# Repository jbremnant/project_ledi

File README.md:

ledi
====

LED Interface (ledi) is an interactive LED display that can communicate with bluetooth devices as well as PC's

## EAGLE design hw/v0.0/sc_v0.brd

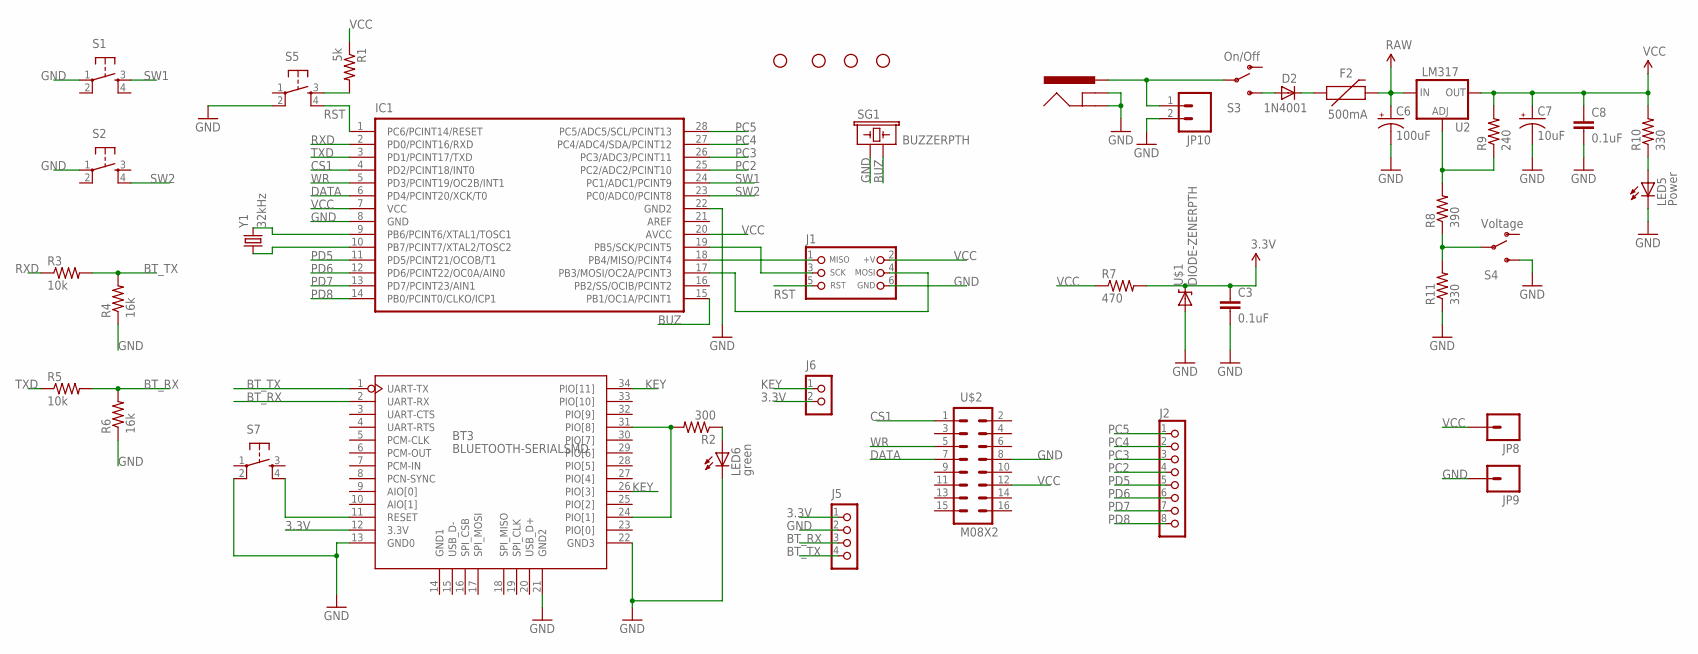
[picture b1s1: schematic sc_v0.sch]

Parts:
BT3: BLUETOOTH-SERIALSMD; SERIAL_BLUETEETH
C3, C8: 0.1uF; CAP-PTH-SMALL2
C6: 100uF; CPOL-RADIAL-100UF-25V
C7: 10uF; CPOL-RADIAL-10UF-25V
D2: 1N4001; DIODE-0.4
F2: 500mA; PTC
IC1: IC_UC_ATMEGA328PDIL; DIL28-N
J1: CON_HEADER_PRG_AVR_ICSP; HEADER_PRG_2X03
J2: CON_HEADER_1X08-PTH; M1X8
J3: POWER_JACKPTH; POWER_JACK_PTH
J5: CON_HEADER_1X04; M1X4
J6: CON_HEADER_1X02-PTH; M1X2
JP1, JP2, JP3, JP4: STAND-OFF
JP8, JP9: M01PTH; 1X01
JP10: M02PTH; 1X02
LED5: Power; LED5MM
LED6: green; LED3MM
R1: 5k; AXIAL-0.3
R2: 300; AXIAL-0.3
R3, R5: 10k; AXIAL-0.3
R4, R6: 16k; AXIAL-0.3
R7: 470; AXIAL-0.3
R8: 390; AXIAL-0.3
R9: 240; AXIAL-0.3
R10, R11: 330; AXIAL-0.3
S1, S2, S5, S7: TAC_SWITCHPTH; TACTILE-PTH
S3: On/Off; SWITCH-SPST
S4: Voltage; SWITCH-SPST
SG1: BUZZERPTH; BUZZER-12MM
U2: LM317; TO220-ADJ
U$1: DIODE-ZENERPTH; DIODE-ZENER
U$2: M08X2; 2X8
Y1: 32kHz; TC38H

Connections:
3.3V: BT3.12 (3.3V), C3.1, J5.1, J6.2, R7.P$2 (2), U$1.P$1 (C)
BT_RX: BT3.2 (UART-RX), J5.3, R5.P$2 (2), R6.P$2 (2)
BT_TX: BT3.1 (UART-TX), J5.4, R3.P$2 (2), R4.P$2 (2)
BUZ: IC1.15 (PB1/OC1A/PCINT1), SG1.- (2)
CS1: IC1.4 (PD2/PCINT18/INT0), U$2.1
DATA: IC1.6 (PD4/PCINT20/XCK/T0), U$2.7
GND: BT3.13 (GND0), BT3.21 (GND2), BT3.22 (GND3), C3.2, C6.2 (-), C7.2 (-), C8.2, IC1.8 (GND), IC1.22 (GND2), J1.6 (GND), J3.GND, J3.GNDBREAK, J5.2, JP9.1, JP10.2, LED5.K (C), LED6.K (C), R4.P$1 (1), R6.P$1 (1), R11.P$1 (1), S1.1, S2.1, S4.3 (S), S5.2, S7.2, SG1.+ (1), U$1.P$2 (A), U$2.8
KEY: BT3.26 (PIO[3]), BT3.34 (PIO[11]), J6.1
unnamed: IC1.9 (PB6/PCINT6/XTAL1/TOSC1), Y1.2
unnamed: IC1.10 (PB7/PCINT7/XTAL2/TOSC2), Y1.1
unnamed: IC1.18 (PB4/MISO/PCINT4), J1.1 (MISO)
unnamed: IC1.19 (PB5/SCK/PCINT5), J1.3 (SCK)
unnamed: IC1.17 (PB3/MOSI/OC2A/PCINT3), J1.4 (MOSI)
unnamed: R8.P$2 (2), R9.P$1 (1), U2.ADJ
unnamed: LED5.A, R10.P$1 (1)
unnamed: BT3.24 (PIO[1]), BT3.31 (PIO[8]), R2.P$2 (2)
unnamed: D2.C, F2.P$1 (1)
unnamed: D2.A, S3.3 (S)
unnamed: J3.PWR, JP10.1, S3.2
unnamed: R8.P$1 (1), R11.P$2 (2), S4.2
unnamed: R1.P$2 (2), S5.3
unnamed: BT3.11 (RESET), S7.4
unnamed: LED6.A, R2.P$1 (1)
PC2: IC1.25 (PC2/ADC2/PCINT10), J2.4
PC3: IC1.26 (PC3/ADC3/PCINT11), J2.3
PC4: IC1.27 (PC4/ADC4/SDA/PCINT12), J2.2
PC5: IC1.28 (PC5/ADC5/SCL/PCINT13), J2.1
PD5: IC1.11 (PD5/PCINT21/OCOB/T1), J2.5
PD6: IC1.12 (PD6/PCINT22/OC0A/AIN0), J2.6
PD7: IC1.13 (PD7/PCINT23/AIN1), J2.7
PD8: IC1.14 (PB0/PCINT0/CLKO/ICP1), J2.8
RAW: C6.1 (+), F2.P$2 (2), U2.IN
RST: IC1.1 (PC6/PCINT14/RESET), J1.5 (RST), S5.4
RXD: IC1.2 (PD0/PCINT16/RXD), R3.P$1 (1)
SW1: IC1.24 (PC1/ADC1/PCINT9), S1.3
SW2: IC1.23 (PC0/ADC0/PCINT8), S2.4
TXD: IC1.3 (PD1/PCINT17/TXD), R5.P$1 (1)
VCC: C7.1 (+), C8.1, IC1.7 (VCC), IC1.20 (AVCC), J1.2 (+V), JP8.1, R1.P$1 (1), R7.P$1 (1), R9.P$2 (2), R10.P$2 (2), U2.OUT, U$2.12
WR: IC1.5 (PD3/PCINT19/OC2B/INT1), U$2.5

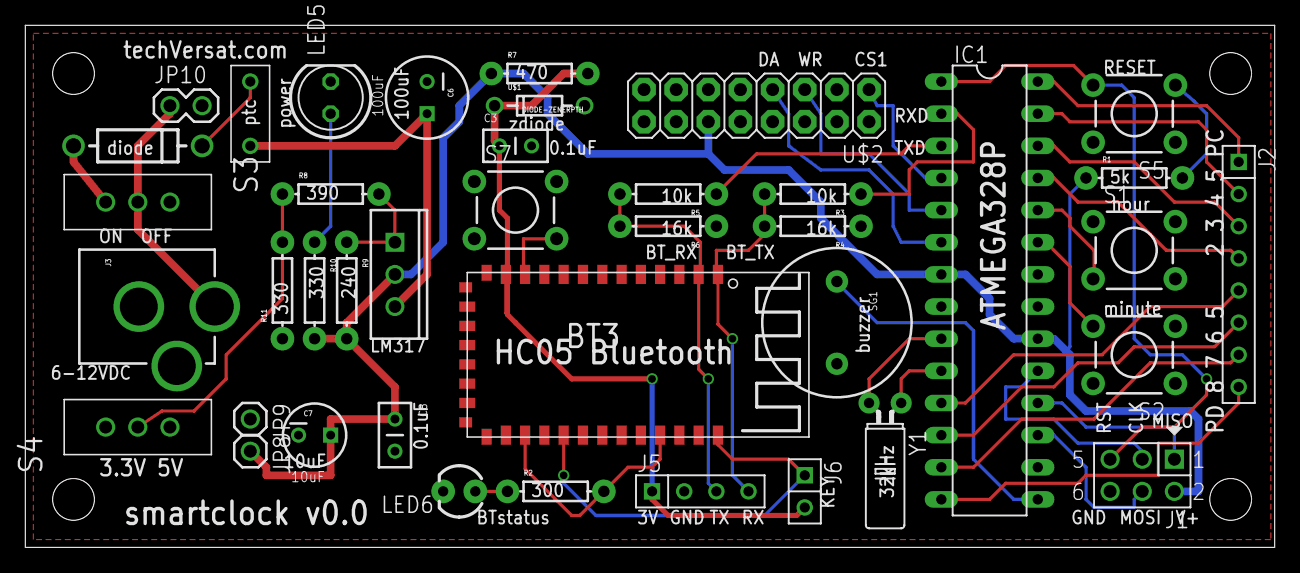
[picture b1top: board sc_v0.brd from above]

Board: 2 copper layers, 98.7 x 41.3 mm, 44 parts (0 on the bottom side), 39 nets.

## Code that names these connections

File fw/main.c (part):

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
// #define USE_V0

#define BUTTON1 PC1
#define BUTTON2 PC0

#ifdef USE_V0
  #define BUZZER_PORT PORTB
  #define BUZZER_REG  DDRB
  #define BUZZER      PB1
#else
  #define BUZZER_PORT PORTD
  #define BUZZER_REG  DDRD
  #define BUZZER      PD6
#endif

#define BT_PRESS 0x02
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ISR(TIMER0_COMPA_vect)
{
  sei();  // enable so we become interruptible
  PORTC ^= (1<<PC4);
  ht1632_syncram_fast(); 
}

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  //  //PCINT14...8 see p70 of datasheet
  PCICR |= (1<<PCIE1);

  //Set the mask on Pin change interrupt 1 so that only PCINT12 (PC4) triggers
  //the interrupt. see p71 of datasheet
  // PCINT17 (PD1) for hours, PCINT19 (PD3) for minutes
  // PC1 / ADC1 / PCINT9
  // PC0 / ADC0 / PCINT8
  PCMSK1 |= (1<<PCINT9) | (1<<PCINT8);

  DDRC  &= ~(1<<BUTTON1);
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
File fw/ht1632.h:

#ifndef _HT1632_HEADER
#define _HT1632_HEADER

#include <avr/io.h>

// for other compilers without uint8_t, change this to char
#define byte  uint8_t
#define byte2 uint16_t

// modify here for more boards
#define N_PANELS    2
#define ALL_BOARDS  0b00000011   // bit mask for active display boards

#define OUTPUT 1
#define INPUT  0
// redefine these macros as necessary : can use ## to concat macro function params
#define PIN_MODE(X,Y,MODE)  if(MODE==1) X |= (1<<Y); else X &= ~(1<<Y)
#define PIN_SET_HIGH(X,Y)   X |= (1<<Y)
#define PIN_SET_LOW(X,Y)    X &= ~(1<<Y)
#define PIN_GET(X,Y)        ( X & (1<<Y) )

// configure stuff here
#define CS1_PORT    PORTD  // CS BoardSelect
#define CS2_PORT    PORTD  // CS BoardSelect
#define RD_PORT     PORTD  // Read Clock
#define WR_PORT     PORTD  // Write Clock
#define DAT_PORT    PORTD  // Write Data
#define DAT_PORT_RD PIND   // Read Data

#define CS1_REG     DDRD
#define CS2_REG     DDRD
#define RD_REG      DDRD
#define WR_REG      DDRD
#define DAT_REG     DDRD

#define CS1_PIN     PD2
#define CS2_PIN     PD5
#define RD_PIN      PD1
#define WR_PIN      PD3
#define DAT_PIN     PD4


/*
 * commands written to the chip consist of a 3 bit "ID", followed by
 * either 9 bits of "Command code" or 7 bits of address + 4 bits of data.
 */
#define HT1632_ID_CMD 4		      /* ID = 100 - Commands */
#define HT1632_ID_RD  6		      /* ID = 110 - Read RAM */
#define HT1632_ID_WR  5		      /* ID = 101 - Write RAM */
#define HT1632_ID_BITS (1<<2)   /* IDs are 3 bits */

#define HT1632_CMD_SYSDIS 0x00	/* CMD= 0000-0000-x Turn off oscil */
#define HT1632_CMD_SYSON  0x01	/* CMD= 0000-0001-x Enable system oscil */
#define HT1632_CMD_LEDOFF 0x02	/* CMD= 0000-0010-x LED duty cycle gen off */
#define HT1632_CMD_LEDON  0x03	/* CMD= 0000-0011-x LEDs ON */
#define HT1632_CMD_BLON   0x09	/* CMD= 0000-1001-x Blink On */
#define HT1632_CMD_BLOFF  0x08	/* CMD= 0000-1000-x Blink Off */
#define HT1632_CMD_SLVMD  0x10	/* CMD= 0001-00xx-x Slave Mode */
#define HT1632_CMD_MSTMD  0x14	/* CMD= 0001-01xx-x Master Mode */
#define HT1632_CMD_RCCLK  0x18	/* CMD= 0001-10xx-x Use on-chip clock */
#define HT1632_CMD_EXTCLK 0x1C	/* CMD= 0001-11xx-x Use external clock */
#define HT1632_CMD_COMS00 0x20	/* CMD= 0010-ABxx-x commons options */
#define HT1632_CMD_COMS01 0x24	/* CMD= 0010-ABxx-x commons options */
#define HT1632_CMD_COMS10 0x28	/* CMD= 0010-ABxx-x commons options */
#define HT1632_CMD_COMS11 0x2C	/* CMD= 0010-ABxx-x commons options */
#define HT1632_CMD_PWM    0xA0	/* CMD= 101x-PPPP-x PWM duty cycle */
#define HT1632_CMD_BITS (1<<7)

// used to pass data associated with plot func
struct plot_addr
{
  byte addr;
  byte csaddr;
  byte bitval;
};

void ht1632_selectboard(byte);
void ht1632_freeboard(void);
void ht1632_writebits(byte, byte);
byte ht1632_readbits(void);
void ht1632_sendcmd(byte, byte);
void ht1632_senddata(byte, byte, byte);
byte ht1632_readdata(byte, byte);
byte ht1632_readreplace(byte, byte, byte);
byte ht1632_setup(byte);
byte2 ht1632_xmax(void);
byte2 ht1632_ymax(void);
void ht1632_getaddr(byte,byte,byte,struct plot_addr*);
void ht1632_plot(byte, byte, byte, byte);
void ht1632_plotram(byte, byte, byte, byte);
void ht1632_editram(byte, byte, byte*, byte);
void ht1632_editram_char(byte, byte, char*, byte, byte);
void ht1632_snapram(void);
void ht1632_syncram(void);
void ht1632_syncram_fast(void);
void ht1632_clearram(void);
byte ht1632_getram(byte, byte);
void ht1632_clear(void);
void ht1632_wipe(byte, byte, byte);
void ht1632_putchar_col(byte, byte, char, byte colstart, byte colend);
void ht1632_putchar(byte, byte, char);
void ht1632_print(byte, byte, const char*);
void ht1632_sendbyte(byte x, byte y, byte dispbyte, byte clear);
void ht1632_scrollstr(const char* str, byte n, byte msec);
void ht1632_putchar2(byte x, byte y, char c, byte offset);
byte ht1632_chcol(unsigned char c, byte j);
char ht1632_whichch(unsigned char c);

#endif

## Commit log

2012-11-10 more docs
2012-11-10 delete
2012-11-11 uart default speed at 9600. suppressed all debug output via uart - it messes up the data flow
2012-11-11 minor code cleanup
2012-11-11 quick rfcomm notes
2012-11-11 more text
2012-11-12 quick edits in parents house
2012-11-12 blah
2012-11-12 first placeholder for LEDI
2012-11-13 small modifications
2012-11-24 bit more docs
2012-11-24 more text for operation
2012-11-26 test
2012-11-26 testing
2012-11-26 added more pics
2012-11-26 changed assembly instruction
2012-11-26 more updates
2012-11-29 add parts for the assembly
2012-11-30 late change
2012-11-30 add more stuff
2012-11-30 fix bugs
2012-12-02 changed the default start up message
2012-12-02 adding css
2012-12-09 finished the assembly tutorial
2012-12-12 started android dev doc
2012-12-13 added more sections, and links
2012-12-13 more changes as per Lyman's suggestions
2012-12-14 add more links
2012-12-17 shuffle the sequence of page02
2012-12-21 ledi android app
2012-12-23 new adds
2012-12-23 added virtual view
2012-12-24 adding changes
2012-12-25 hopefully bug free
2012-12-25 fixed a bug
2012-12-25 made the dot plotting more efficient
2012-12-25 added mac os x link
2012-12-25 simple modify
2012-12-26 add more stuff to the page02
2012-12-26 almost done
2012-12-26 more changes for bound service implementation
2012-12-27 oops forgot to initialize the textView
2012-12-27 made the app more robust, supports latest android now
2012-12-29 gmail more robust
2012-12-29 more
2012-12-29 shuffled around the source
2012-12-29 because we shuffled around

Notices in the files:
parts and their libraries:
SparkFun: Licensing: CC v3.0 Share-Alike You are welcome to use this library for commercial purposes.
